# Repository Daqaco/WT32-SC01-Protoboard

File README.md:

# WT32-SC01-Protoboard
A prototype board for the WT32-SC01 Touch Display
Schematic and board done with Eagle 9.x.
Daughter board attaches to the display header on the long edge.  Power and Gnd broken out on the upper pins, remaining ports on the pins to the left and right.

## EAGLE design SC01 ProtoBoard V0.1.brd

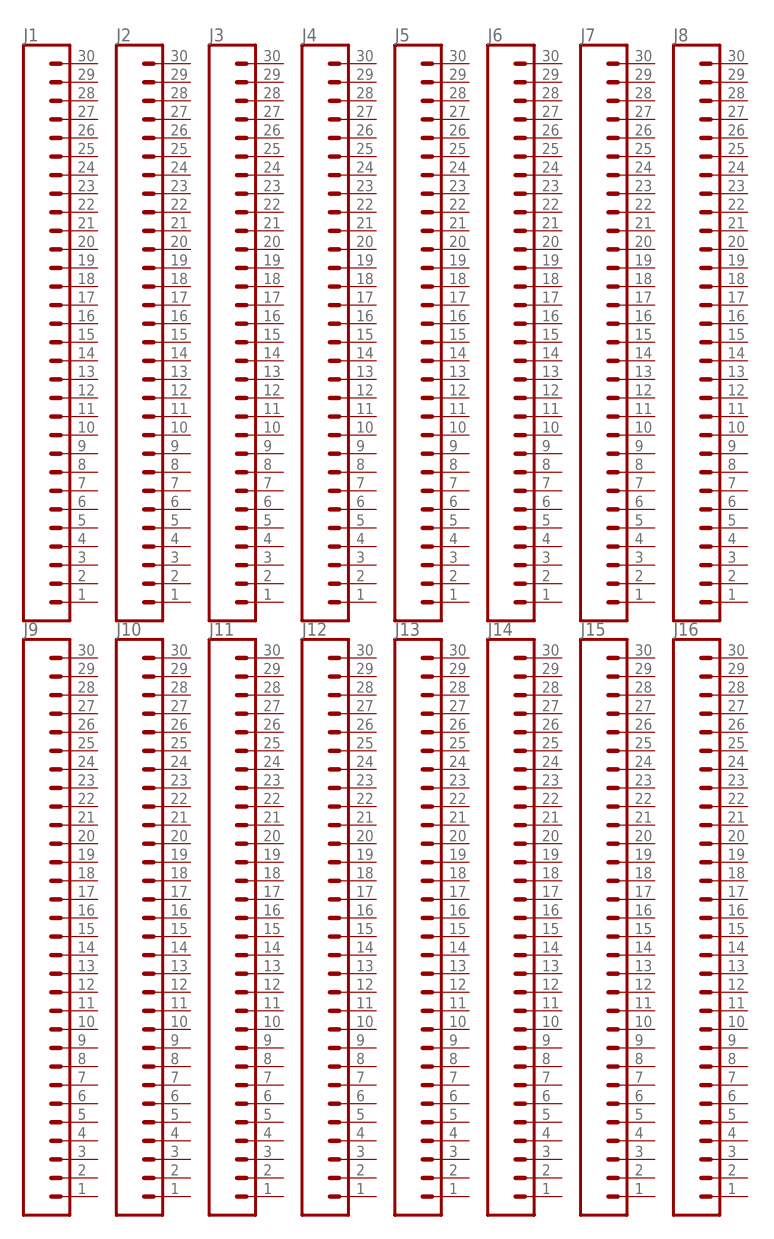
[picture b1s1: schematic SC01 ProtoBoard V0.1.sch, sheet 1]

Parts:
J1, J2, J3, J4, J5, J6, J7, J8, J9, J10, J11, J12, J13, J14, J15, J16: CONN_30NO_SILK; 1X30_NO_SILK

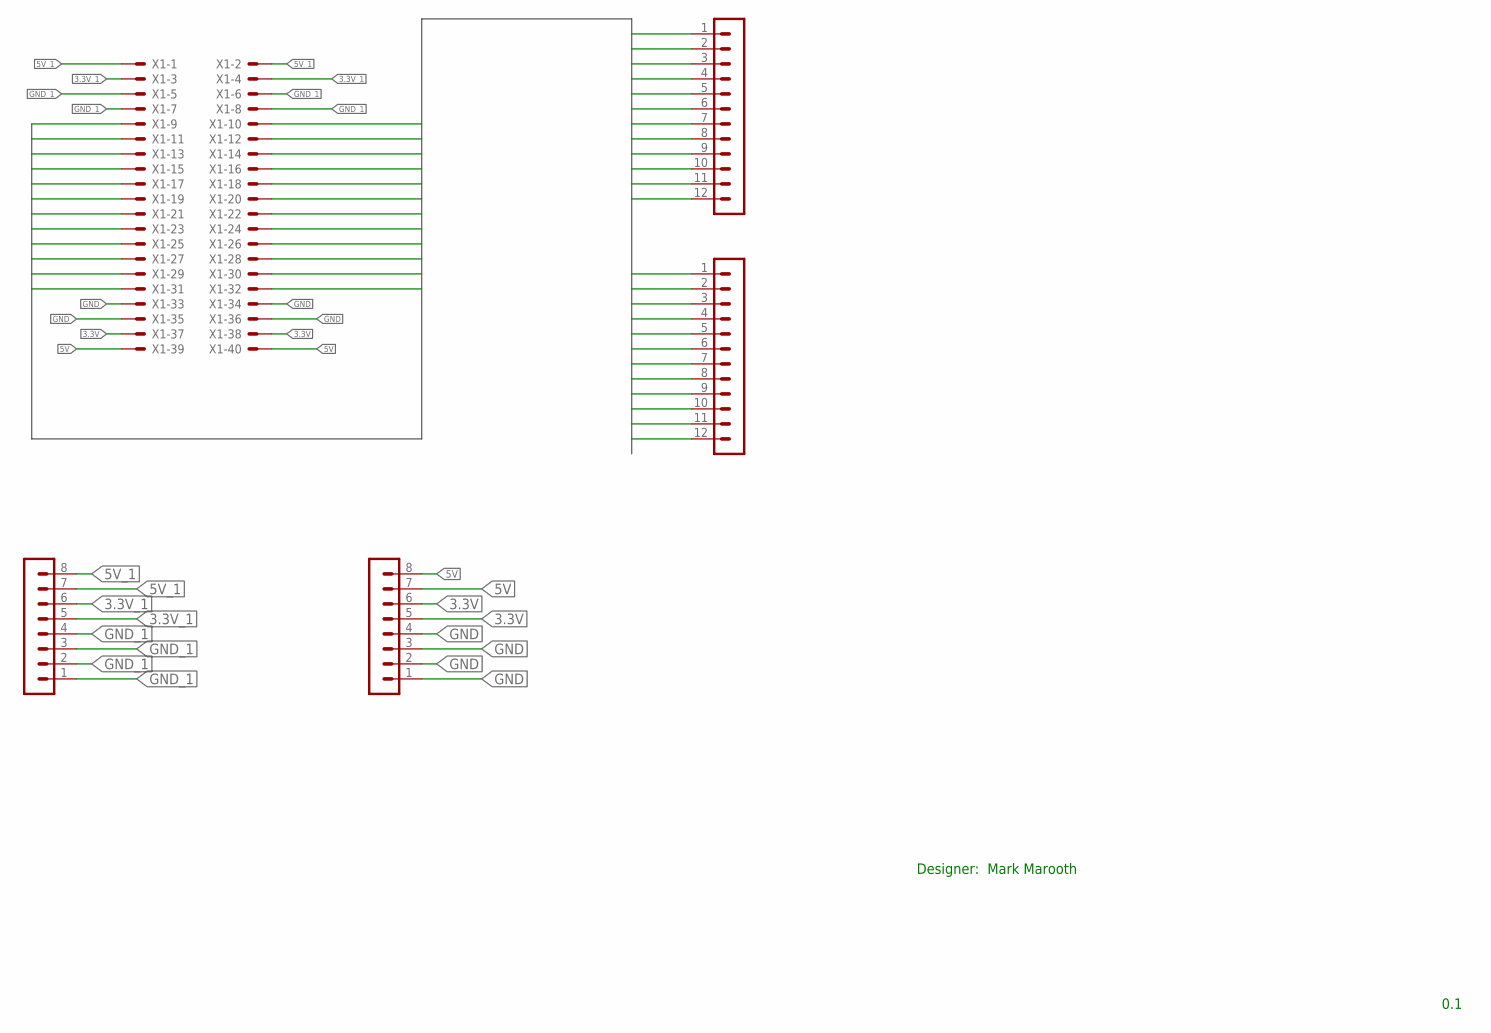
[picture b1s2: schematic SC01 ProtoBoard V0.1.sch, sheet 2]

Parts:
HDR1, HDR2: MA12-1
HDR3, HDR4: MA08-1
X1: 87758-4016

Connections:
3.3V: HDR4.5, HDR4.6, X1.37, X1.38
3.3V_1: HDR3.5, HDR3.6, X1.3, X1.4
5V: HDR4.7, HDR4.8, X1.39, X1.40
5V_1: HDR3.7, HDR3.8, X1.1, X1.2
GND: HDR4.1, HDR4.2, HDR4.3, HDR4.4, X1.33, X1.34, X1.35, X1.36
GND_1: HDR3.1, HDR3.2, HDR3.3, HDR3.4, X1.5, X1.6, X1.7, X1.8
PHEADER9: HDR1.1, X1.9
PHEADER10: HDR1.2, X1.10
PHEADER11: HDR1.3, X1.11
PHEADER12: HDR1.4, X1.12
PHEADER13: HDR1.5, X1.13
PHEADER14: HDR1.6, X1.14
PHEADER15: HDR1.7, X1.15
PHEADER16: HDR1.8, X1.16
PHEADER17: HDR1.9, X1.17
PHEADER18: HDR1.10, X1.18
PHEADER19: HDR1.11, X1.19
PHEADER20: HDR1.12, X1.20
PHEADER21: HDR2.1, X1.21
PHEADER22: HDR2.2, X1.22
PHEADER23: HDR2.3, X1.23
PHEADER24: HDR2.4, X1.24
PHEADER25: HDR2.5, X1.25
PHEADER26: HDR2.6, X1.26
PHEADER27: HDR2.7, X1.27
PHEADER28: HDR2.8, X1.28
PHEADER29: HDR2.9, X1.29
PHEADER30: HDR2.10, X1.30
PHEADER31: HDR2.11, X1.31
PHEADER32: HDR2.12, X1.32

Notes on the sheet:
Designer: Mark Marooth
0.1

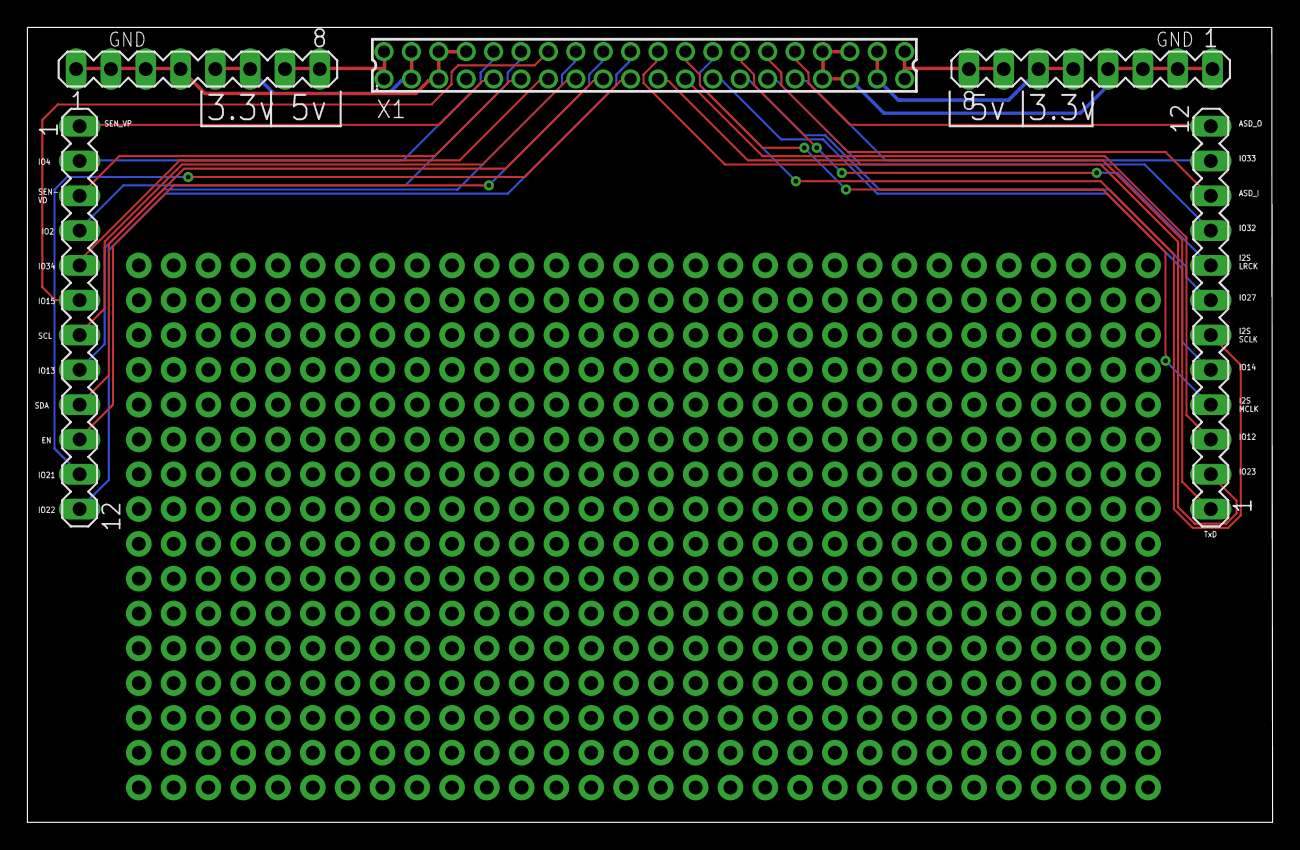
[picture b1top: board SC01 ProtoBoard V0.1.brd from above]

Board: 2 copper layers, 90.9 x 58.0 mm, 21 parts (0 on the bottom side), 30 nets.

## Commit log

2022-02-25 Add files via upload
    Initial Upload.

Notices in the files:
parts and their libraries:
SparkFun-Connectors: Licensing: Creative Commons ShareAlike 4.0 International - https://creativecommons.org/licenses/by-sa/4.0
